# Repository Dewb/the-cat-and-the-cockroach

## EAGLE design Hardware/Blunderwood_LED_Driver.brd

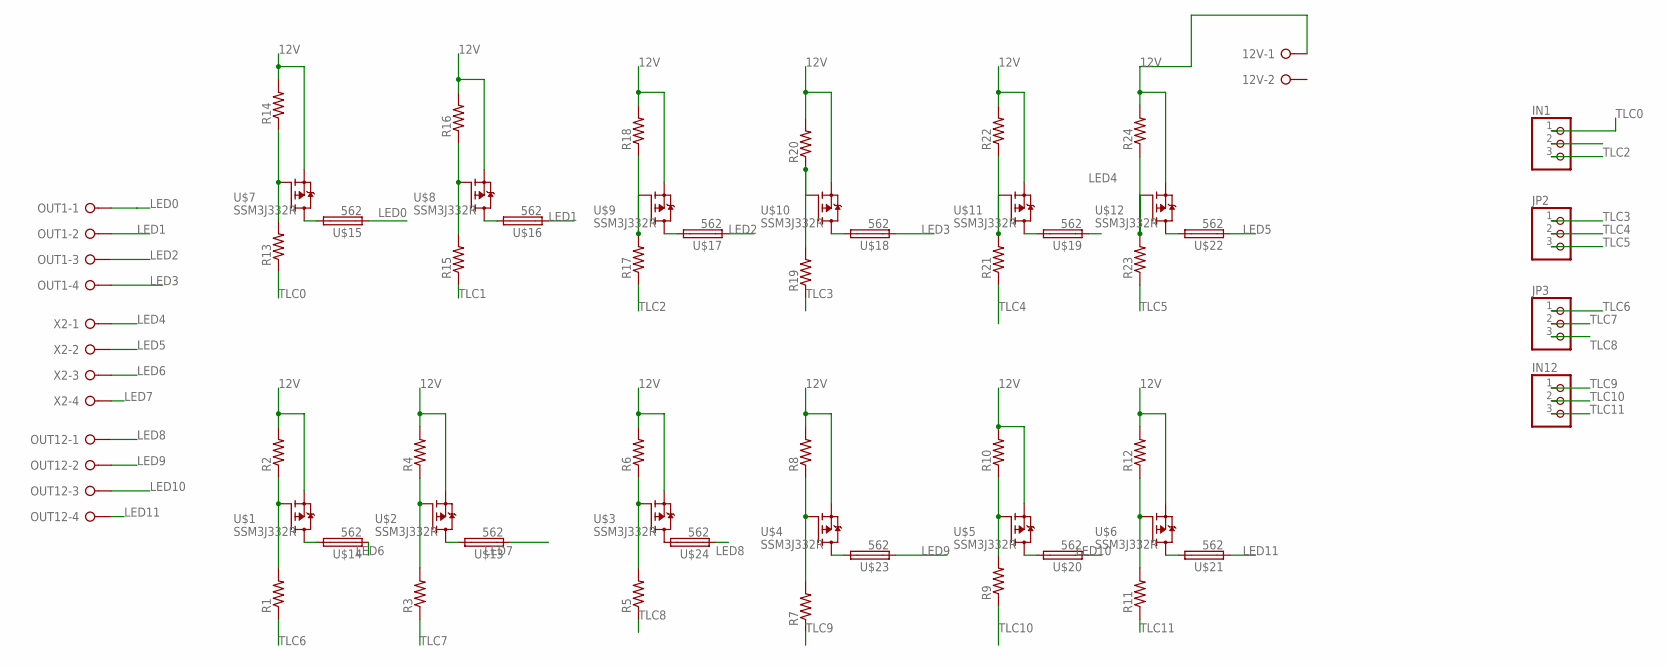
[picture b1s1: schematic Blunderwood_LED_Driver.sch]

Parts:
12V: W237-02P; W237-132
IN1, IN12: PINHD-1X3; 1X03
JP2, JP3: PINHD-1X3; 1X03
OUT1, OUT12: W237-04P; W237-4P
R1, R2, R3, R4, R5, R6, R7, R8, R9, R10, R11, R12, R13, R14, R15, R16, R17, R18, R19, R20, R21, R22, R23, R24: R-US_R0805; R0805
U$1, U$2, U$3, U$4, U$5, U$6, U$7, U$8, U$9, U$10, U$11, U$12: SSM3J332R; SOT23
U$13, U$14, U$15, U$16, U$17, U$18, U$19, U$20, U$21, U$22, U$23, U$24: 562; 564
X2: W237-04P; W237-4P

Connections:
12V: 12V.1, R2.2, R4.2, R6.2, R8.2, R10.2, R12.2, R14.2, R16.2, R18.2, R20.2, R22.2, R24.2, U$1.2 (S), U$2.2 (S), U$3.2 (S), U$4.2 (S), U$5.2 (S), U$6.2 (S), U$7.2 (S), U$8.2 (S), U$9.2 (S), U$10.2 (S), U$11.2 (S), U$12.2 (S)
LED0: OUT1.1, U$15.P$3 (1)
LED1: OUT1.2, U$16.P$3 (1)
LED2: OUT1.3, U$17.P$3 (1)
LED3: OUT1.4, U$18.P$3 (1)
LED4: U$19.P$3 (1), X2.1
LED5: U$22.P$3 (1), X2.2
LED6: U$14.P$3 (1), X2.3
LED7: U$13.P$3 (1), X2.4
LED8: OUT12.1, U$24.P$3 (1)
LED9: OUT12.2, U$23.P$3 (1)
LED10: OUT12.3, U$20.P$3 (1)
LED11: OUT12.4, U$21.P$3 (1)
unnamed: R1.2, R2.1, U$1.1 (G)
unnamed: U$1.3 (D), U$14.P$4 (2)
unnamed: R3.2, R4.1, U$2.1 (G)
unnamed: R5.2, R6.1, U$3.1 (G)
unnamed: R7.2, R8.1, U$4.1 (G)
unnamed: U$4.3 (D), U$23.P$4 (2)
unnamed: U$2.3 (D), U$13.P$4 (2)
unnamed: U$3.3 (D), U$24.P$4 (2)
unnamed: R13.2, R14.1, U$7.1 (G)
unnamed: U$7.3 (D), U$15.P$4 (2)
unnamed: R9.2, R10.1, U$5.1 (G)
unnamed: U$5.3 (D), U$20.P$4 (2)
unnamed: R11.2, R12.1, U$6.1 (G)
unnamed: U$6.3 (D), U$21.P$4 (2)
unnamed: R15.2, R16.1, U$8.1 (G)
unnamed: U$8.3 (D), U$16.P$4 (2)
unnamed: R17.2, R18.1, U$9.1 (G)
unnamed: R19.2, R20.1, U$10.1 (G)
unnamed: U$10.3 (D), U$18.P$4 (2)
unnamed: R21.2, R22.1, U$11.1 (G)
unnamed: R23.2, R24.1, U$12.1 (G)
unnamed: U$12.3 (D), U$22.P$4 (2)
unnamed: U$9.3 (D), U$17.P$4 (2)
unnamed: U$11.3 (D), U$19.P$4 (2)
TLC0: IN1.1, R13.1
TLC1: IN1.2, R15.1
TLC2: IN1.3, R17.1
TLC3: JP2.1, R19.1
TLC4: JP2.2, R21.1
TLC5: JP2.3, R23.1
TLC6: JP3.1, R1.1
TLC7: JP3.2, R3.1
TLC8: JP3.3, R5.1
TLC9: IN12.1, R7.1
TLC10: IN12.2, R9.1
TLC11: IN12.3, R11.1

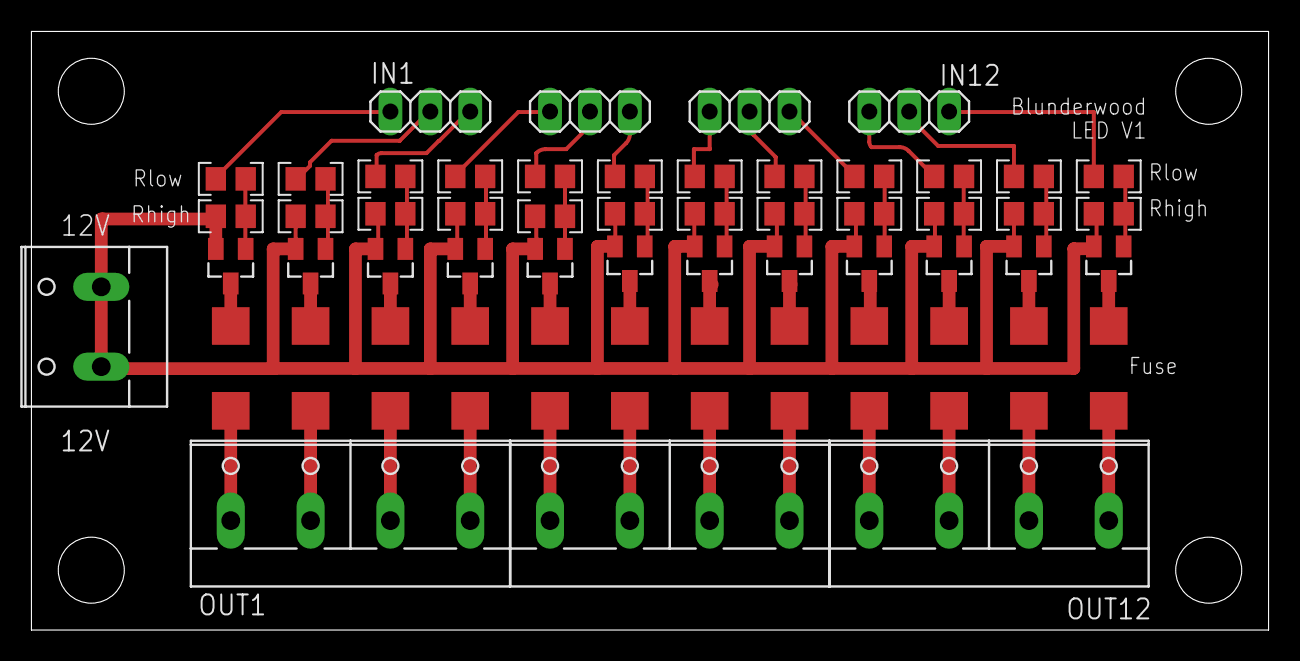
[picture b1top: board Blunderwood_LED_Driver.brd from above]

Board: 2 copper layers, 78.7 x 38.1 mm, 56 parts (0 on the bottom side), 49 nets.

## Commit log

2014-12-01 Initial commit, estimate letterpress block quantities
2014-12-01 Reverse sort count, forward sort letter
2014-12-01 Remove unnecessary import
2015-07-19 Added Basic Arduino Code
2015-07-19 Adding Schematics and PCB designs
2015-07-19 Reorganize for new work
2015-07-19 Figment linotype layout
2015-07-22 Adjustable blocks per line
2015-07-22 Linocut tiles for Figment
2015-07-25 Estimate additional blocktype reqs for playa
2015-07-25 Reorganize letterpress files
2015-07-25 Prototype serial data display server
2015-07-26 Correct text display on screen
2015-07-26 Adjust screen line length
2015-07-26 Log input
2015-07-26 Connect to Arduion and receive real keystrokes
2015-07-26 Clean up flow, autodetect Arduino port name (on OSX)
2015-07-26 Add startup scripts
2015-07-28 Platform-specific serial port paths
2015-08-08 Fix bottom line horizontal scrolling
2015-08-08 Linocut files for additional poems
2015-08-24 Add sound support
2015-08-24 Start backspace support
2015-08-25 Refactor for client-side modes
2015-08-25 Backspace prototype
2015-08-25 Cleaner backspace implementation approach
2015-08-25 Correctly functioning backspace implementation
2015-08-26 Refactor for server-side modes
2015-08-26 RepeatMessage server mode
2015-08-27 Implement basic control panel
2015-08-27 Integrate Valoch screen mode from earlier prototype
2015-08-27 Options grid display
2015-08-30 Editable options grid prototype
2015-08-30 possible poems for automated mode
2015-08-30 Log path for ubuntu
2015-08-30 Log path for ubuntu (reapply post 'theirs' merge)
2015-08-31 Re-enable default text
2015-08-31 Properly manage serial device hotplugging
2015-08-31 Fix race condition in sound buffering
2015-09-02 On playa screen adjustments, fix backspace alignment issue
2015-09-02 Translate extended ASCII correctly
2015-09-02 Prevent cursor from appearing over display screen
2015-09-02 Fix warning
2015-09-02 Always play carriage sound regardless of prev line length
2020-05-01 post-install changes
2020-05-01 Rescue logfile from mintbox
